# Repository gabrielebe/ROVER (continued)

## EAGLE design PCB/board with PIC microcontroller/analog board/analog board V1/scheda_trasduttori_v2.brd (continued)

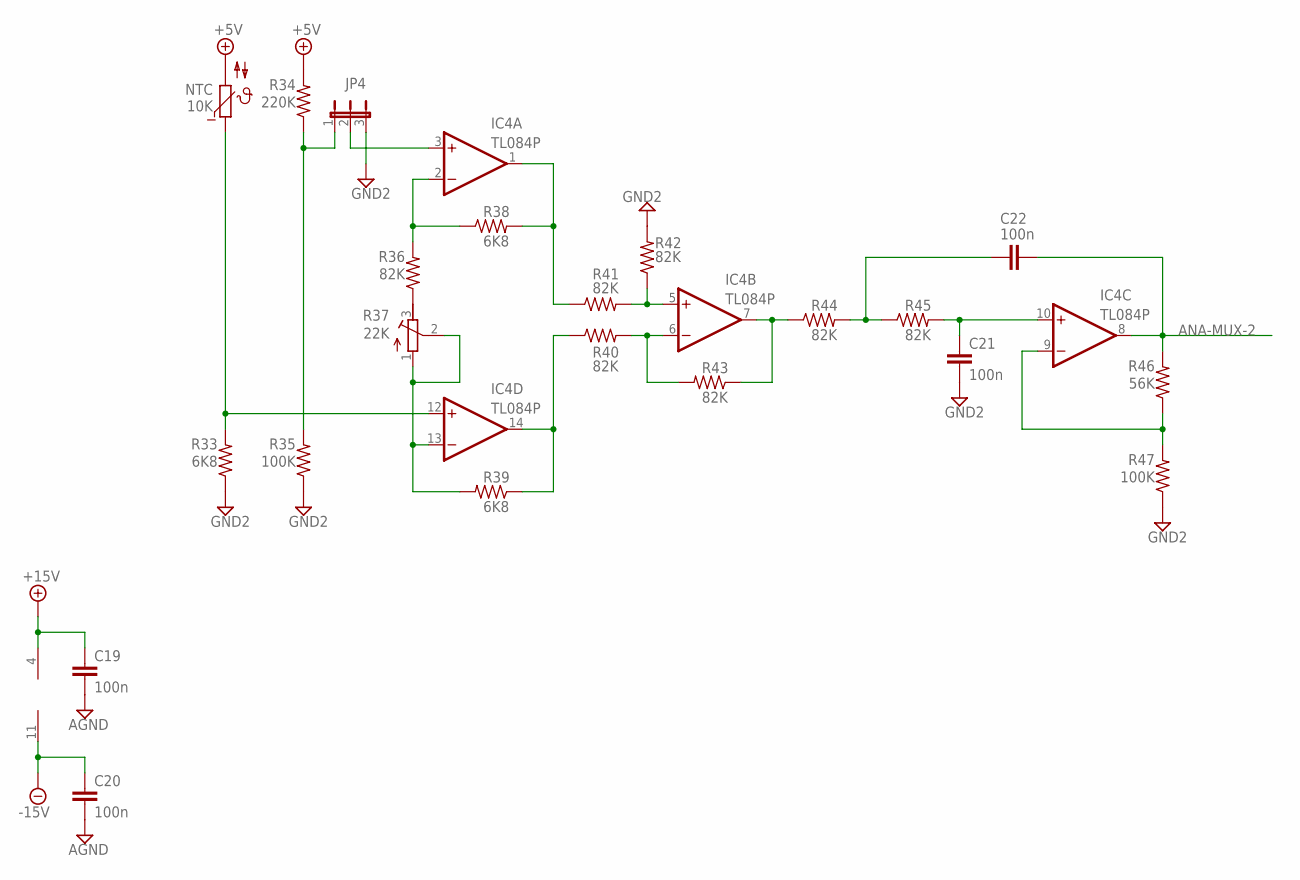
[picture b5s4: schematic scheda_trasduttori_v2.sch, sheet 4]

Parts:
C19, C20, C21, C22: 100n; C025-025X050
IC4: TL084P; DIL14
JP4: JP2E; JP2
NTC: 10K; P640
R33, R38, R39: 6K8; 0204/7
R34: 220K; 0204/7
R35, R47: 100K; 0204/7
R36, R40, R41, R42, R43, R44, R45: 82K; 0204/7
R37: 22K; RTRIM64W
R46: 56K; 0204/7

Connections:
+5V: NTC.2, R34.2; also elsewhere on the board
+15V: C19.1, IC4.4 (V+); also elsewhere on the board
-15V: C20.1, IC4.11 (V-); also elsewhere on the board
AGND: C19.2, C20.2; also elsewhere on the board
ANA-MUX-2: C22.2, IC4.8 (OUT), R46.2; also elsewhere on the board
GND2: C21.2, JP4.3, R33.1, R35.1, R42.2, R47.1; also elsewhere on the board
unnamed: C21.1, IC4.10 (+IN), R45.2
unnamed: IC4.9 (-IN), R46.1, R47.2
unnamed: C22.1, R44.2, R45.1
unnamed: IC4.12 (+IN), NTC.1, R33.2
unnamed: R36.1, R37.3 (A)
unnamed: IC4.2 (-IN), R36.2, R38.1
unnamed: IC4.1 (OUT), R38.2, R40.1
unnamed: IC4.13 (-IN), R37.1 (E), R37.2 (S), R39.2
unnamed: IC4.14 (OUT), R39.1, R41.1
unnamed: IC4.6 (-IN), R41.2, R43.2
unnamed: IC4.5 (+IN), R40.2, R42.1
unnamed: IC4.7 (OUT), R43.1, R44.1
unnamed: JP4.1, R34.1, R35.2
unnamed: IC4.3 (+IN), JP4.2

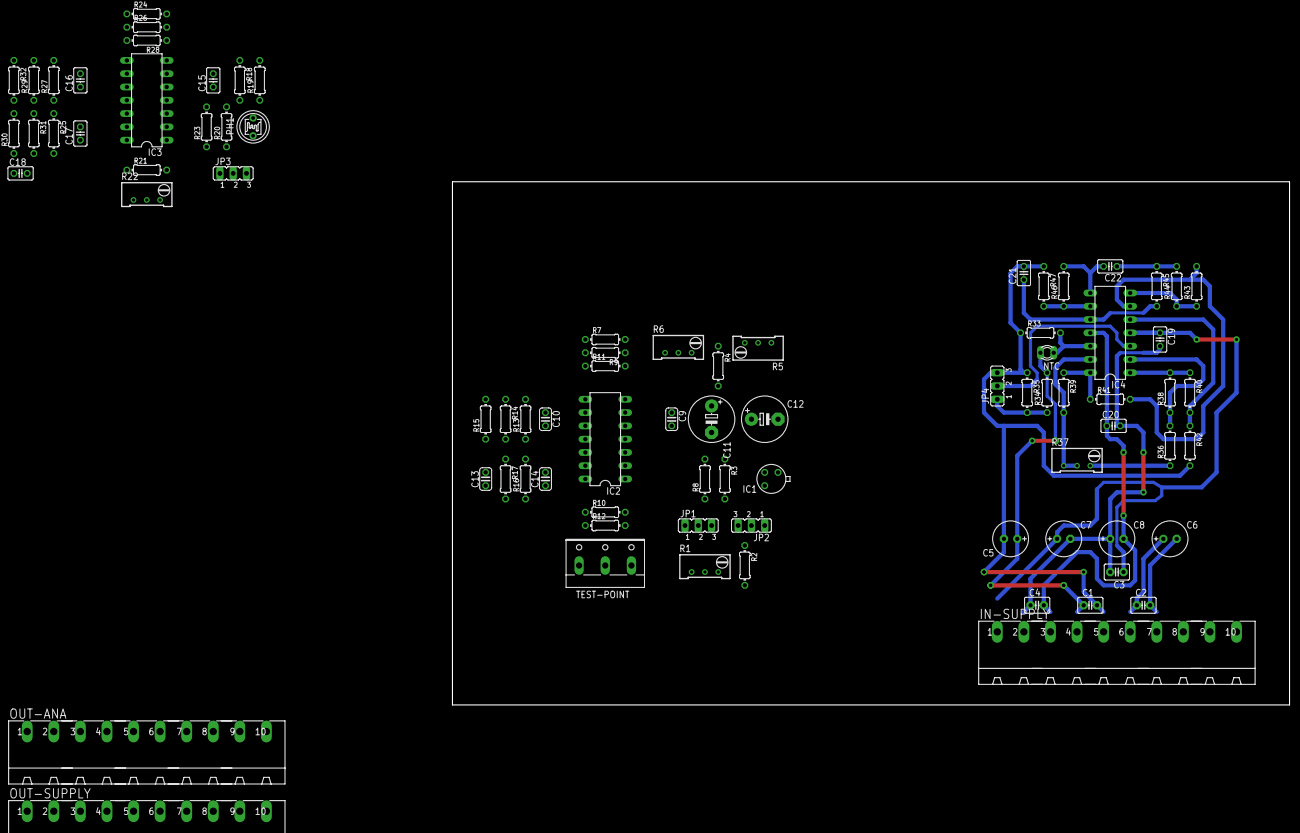
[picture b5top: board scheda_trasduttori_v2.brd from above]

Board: 2 copper layers, 160.0 x 100.0 mm, 83 parts (0 on the bottom side), 56 nets.

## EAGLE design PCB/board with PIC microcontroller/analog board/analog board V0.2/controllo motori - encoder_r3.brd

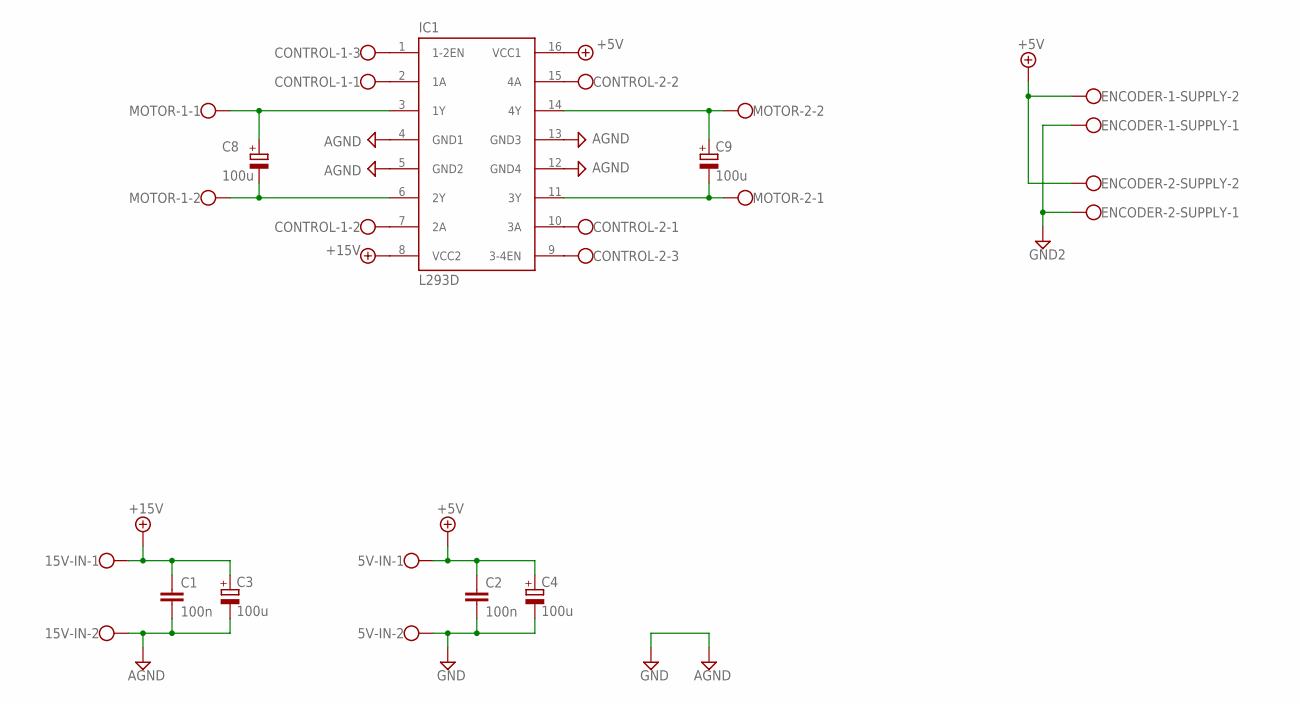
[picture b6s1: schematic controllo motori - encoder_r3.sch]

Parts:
5V-IN, 15V-IN: W237-102
C1, C2: 100n; C025-025X050
C3, C4, C8, C9: 100u; B45181B
CONTROL-1, CONTROL-2: W237-103
ENCODER-1-SUPPLY, ENCODER-2-SUPPLY: W237-102
IC1: L293D; DIL16
MOTOR-1, MOTOR-2: W237-102

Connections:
+5V: 5V-IN.1, C2.1, C4.+, ENCODER-1-SUPPLY.2, ENCODER-2-SUPPLY.2, IC1.16 (VCC1)
+15V: 15V-IN.1, C1.1, C3.+, IC1.8 (VCC2)
AGND: 15V-IN.2, C1.2, C3.-, IC1.4 (GND1), IC1.5 (GND2), IC1.12 (GND4), IC1.13 (GND3)
GND: 5V-IN.2, C2.2, C4.-
GND2: ENCODER-1-SUPPLY.1, ENCODER-2-SUPPLY.1
unnamed: C8.+, IC1.3 (1Y), MOTOR-1.1
unnamed: C8.-, IC1.6 (2Y), MOTOR-1.2
unnamed: C9.-, IC1.11 (3Y), MOTOR-2.1
unnamed: C9.+, IC1.14 (4Y), MOTOR-2.2
unnamed: CONTROL-1.1, IC1.2 (1A)
unnamed: CONTROL-1.2, IC1.7 (2A)
unnamed: CONTROL-1.3, IC1.1 (1-2EN)
unnamed: CONTROL-2.3, IC1.9 (3-4EN)
unnamed: CONTROL-2.1, IC1.10 (3A)
unnamed: CONTROL-2.2, IC1.15 (4A)

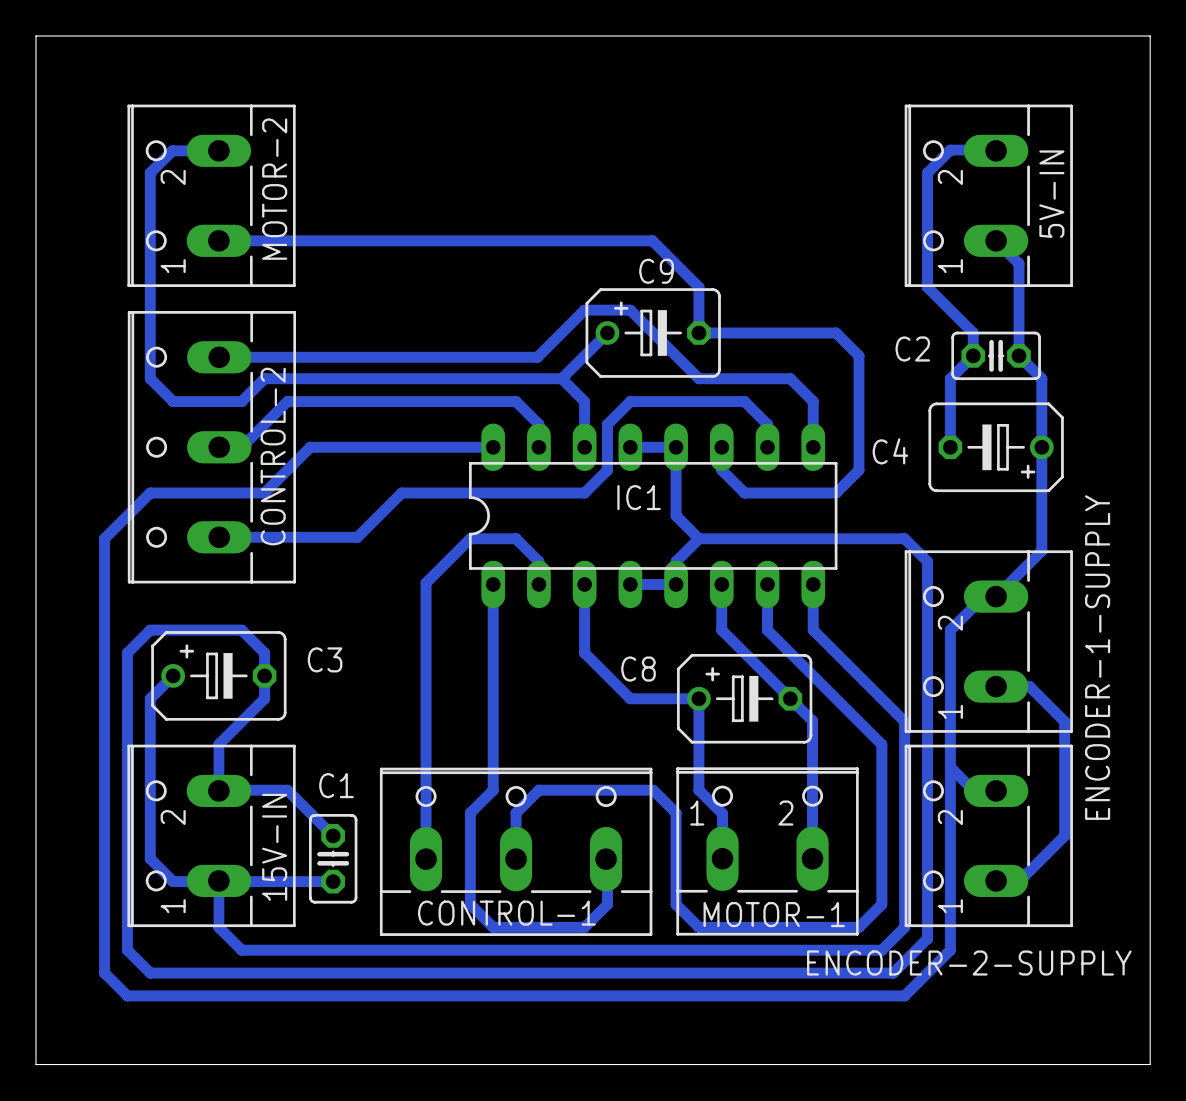
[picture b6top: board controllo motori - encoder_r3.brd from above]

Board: 2 copper layers, 61.9 x 57.1 mm, 15 parts (0 on the bottom side), 15 nets.

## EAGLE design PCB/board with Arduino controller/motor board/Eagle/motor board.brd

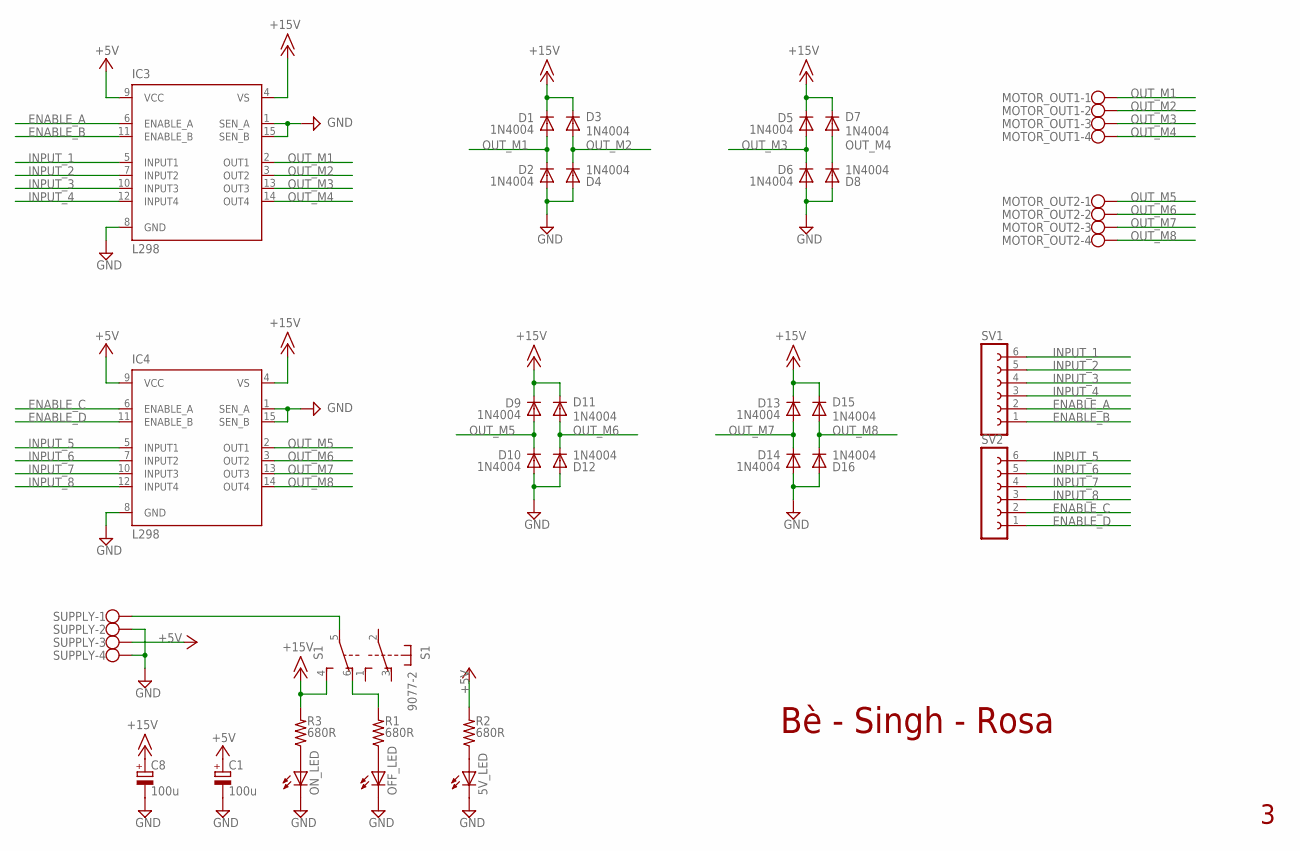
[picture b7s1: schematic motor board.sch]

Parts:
5V_LED: LED5MM
C1: 100u; E2,5-7
C8: 100u; E3,5-8
D1, D2, D3, D4, D5, D6, D7, D8, D9, D10, D11, D12, D13, D14, D15, D16: 1N4004; DO41-10
IC3, IC4: L298; MULTIWATT-15
MOTOR_OUT1, MOTOR_OUT2: W237-4
OFF_LED: LED5MM
ON_LED: LED5MM
R1, R2, R3: 680R; 0207/10
S1: 9077-2
SUPPLY: W237-4
SV1, SV2: FE06-1; FE06

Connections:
+5V: C1.+, IC3.9 (VCC), IC4.9 (VCC), R2.2, SUPPLY.3
+15V: C8.+, D1.C, D3.C, D5.C, D7.C, D9.C, D11.C, D13.C, D15.C, IC3.4 (VS), IC4.4 (VS), R3.2, S1.4 (S)
ENABLE_A: IC3.6 (ENABLE_A), SV1.2
ENABLE_B: IC3.11 (ENABLE_B), SV1.1
ENABLE_C: IC4.6 (ENABLE_A), SV2.2
ENABLE_D: IC4.11 (ENABLE_B), SV2.1
GND: 5V_LED.K (C), C1.-, C8.-, D2.A, D4.A, D6.A, D8.A, D10.A, D12.A, D14.A, D16.A, IC3.1 (SEN_A), IC3.8 (GND), IC3.15 (SEN_B), IC4.1 (SEN_A), IC4.8 (GND), IC4.15 (SEN_B), OFF_LED.K (C), ON_LED.K (C), SUPPLY.2, SUPPLY.4
INPUT_1: IC3.5 (INPUT1), SV1.6
INPUT_2: IC3.7 (INPUT2), SV1.5
INPUT_3: IC3.10 (INPUT3), SV1.4
INPUT_4: IC3.12 (INPUT4), SV1.3
INPUT_5: IC4.5 (INPUT1), SV2.6
INPUT_6: IC4.7 (INPUT2), SV2.5
INPUT_7: IC4.10 (INPUT3), SV2.4
INPUT_8: IC4.12 (INPUT4), SV2.3
unnamed: ON_LED.A, R3.1
unnamed: OFF_LED.A, R1.1
unnamed: 5V_LED.A, R2.1
unnamed: S1.5, SUPPLY.1
unnamed: R1.2, S1.6 (O)
OUT_M1: D1.A, D2.C, IC3.2 (OUT1), MOTOR_OUT1.1
OUT_M2: D3.A, D4.C, IC3.3 (OUT2), MOTOR_OUT1.2
OUT_M3: D5.A, D6.C, IC3.13 (OUT3), MOTOR_OUT1.3
OUT_M4: D7.A, D8.C, IC3.14 (OUT4), MOTOR_OUT1.4
OUT_M5: D9.A, D10.C, IC4.2 (OUT1), MOTOR_OUT2.1
OUT_M6: D11.A, D12.C, IC4.3 (OUT2), MOTOR_OUT2.2
OUT_M7: D13.A, D14.C, IC4.13 (OUT3), MOTOR_OUT2.3
OUT_M8: D15.A, D16.C, IC4.14 (OUT4), MOTOR_OUT2.4

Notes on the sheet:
Bè - Singh - Rosa

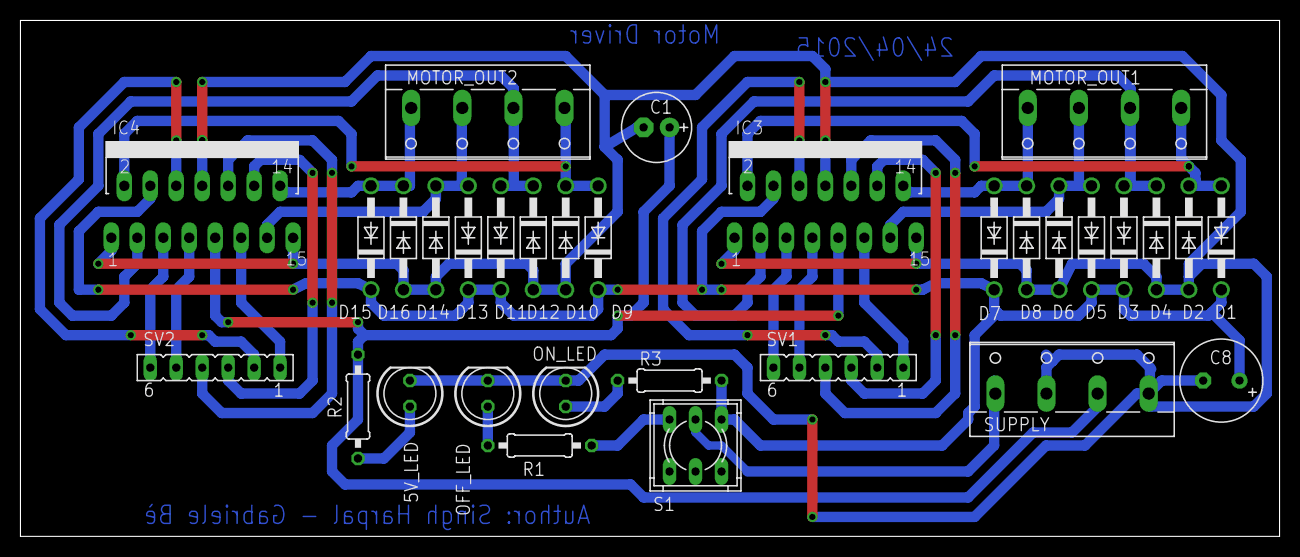
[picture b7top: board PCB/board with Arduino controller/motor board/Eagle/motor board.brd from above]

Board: 2 copper layers, 123.2 x 50.5 mm, 32 parts (0 on the bottom side), 28 nets.

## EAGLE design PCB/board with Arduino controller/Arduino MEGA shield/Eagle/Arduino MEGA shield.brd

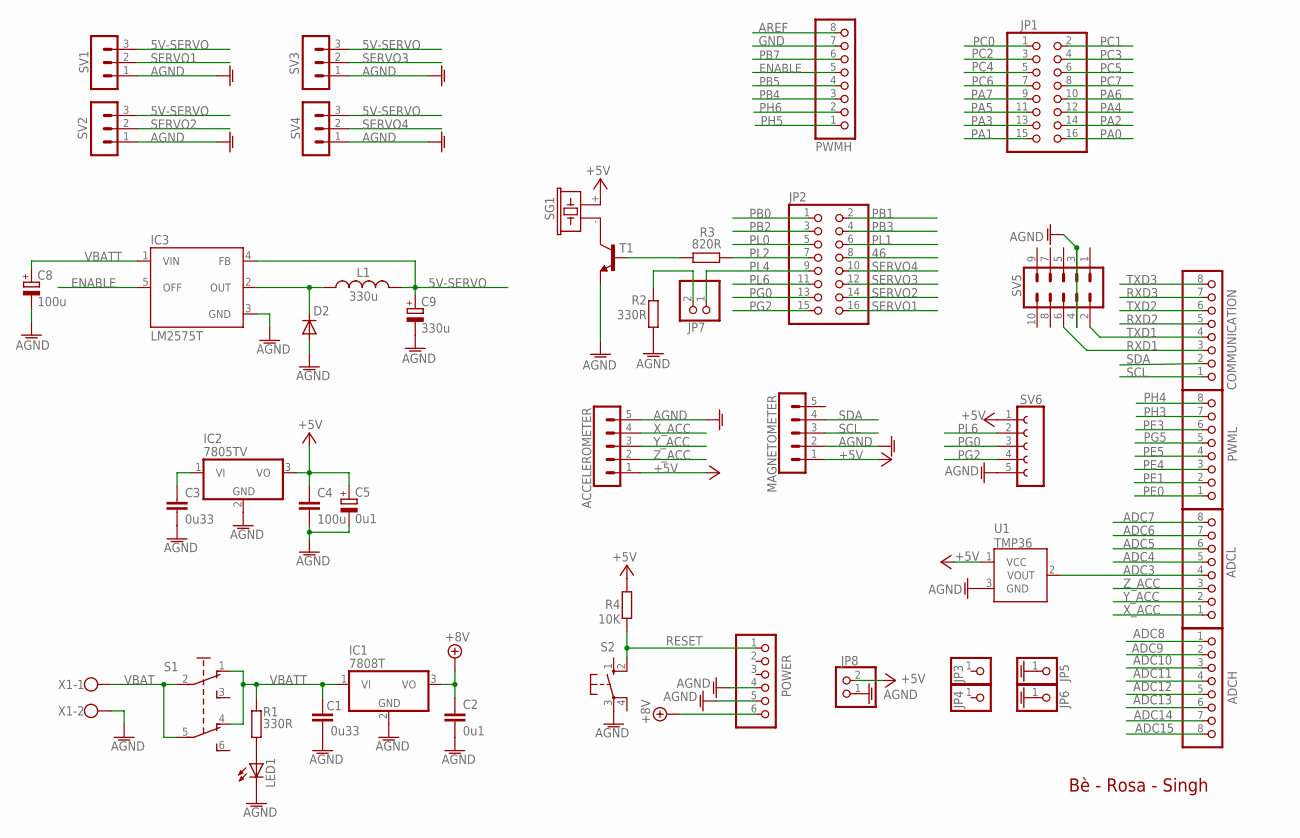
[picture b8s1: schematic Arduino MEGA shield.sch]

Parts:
ACCELEROMETER: MA05-1
ADCH: PINHD-1X8; 1X08
ADCL: PINHD-1X8; 1X08
C1, C3: 0u33; C050-035X075
C2: 0u1; C050-035X075
C4: 100u; C050-035X075
C5: 0u1; E2,5-7
C8: 100u; E3,5-8
C9: 330u; E3,5-8
COMMUNICATION: PINHD-1X8; 1X08
D2: 1N5819; DO35-10
IC1: 7808T; TO220H
IC2: 7805TV; TO220V
IC3: LM2575T; TO220-5
JP1, JP2: PINHD-2X8; 2X08
JP3, JP4, JP5, JP6: PINHD-1X1; 1X01
JP7, JP8: PINHD-1X2; 1X02
L1: 330u; AXIAL-0.6
LED1: LED5MM
MAGNETOMETER: MA05-1
POWER: PINHD-1X6; 1X06
PWMH: PINHD-1X8; 1X08
PWML: PINHD-1X8; 1X08
R1, R2: 330R; 0207/10
R3: 820R; 0207/10
R4: 10K; 0207/10
S1: TL46PO; TL4XPO
S2: 10-XX; B3F-10XX
SG1: F/CM12P
SV1, SV2, SV3, SV4: MA03-1
SV5: MA05-2
SV6: FE05-1
T1: BC547A-NPN-TO92-CBE; TO92-CBE
U1: TMP36; TO-92
X1: W237-102

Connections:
5V-SERVO: C9.+, IC3.4 (FB), L1.P$2 (2), SV1.3, SV2.3, SV3.3, SV4.3
46: JP2.8
+5V: ACCELEROMETER.1, C4.1, C5.+, IC2.3 (VO), JP8.2, MAGNETOMETER.1, R4.2, SG1.+ (1), SV6.1, U1.1 (VCC)
+8V: C2.1, IC1.3 (VO), POWER.6
ADC3: ADCL.4, U1.2 (VOUT)
ADC4: ADCL.5
ADC5: ADCL.6
ADC6: ADCL.7
ADC7: ADCL.8
ADC8: ADCH.1
ADC9: ADCH.2
ADC10: ADCH.3
ADC11: ADCH.4
ADC12: ADCH.5
ADC13: ADCH.6
ADC14: ADCH.7
ADC15: ADCH.8
AGND: ACCELEROMETER.5, C1.2, C2.2, C3.2, C4.2, C5.-, C8.-, C9.-, D2.A, IC1.2 (GND), IC2.2 (GND), IC3.3 (GND), JP5.1, JP6.1, JP8.1, LED1.K (C), MAGNETOMETER.2, POWER.4, POWER.5, R2.2, S2.3, SV1.1, SV2.1, SV3.1, SV4.1, SV5.3, SV5.4, SV6.5, T1.E, U1.3 (GND), X1.2
AREF: PWMH.8
ENABLE: IC3.5 (OFF), PWMH.5
GND: PWMH.7
unnamed: JP7.2, R2.1
unnamed: LED1.A, R1.1
unnamed: C3.1, IC2.1 (VI)
unnamed: R3.1, T1.B
unnamed: D2.C, IC3.2 (OUT), L1.P$1 (1)
unnamed: SG1.- (2), T1.C
PA0: JP1.16
PA1: JP1.15
PA2: JP1.14
PA3: JP1.13
PA4: JP1.12
PA5: JP1.11
PA6: JP1.10
PA7: JP1.9
PB0: JP2.1
PB1: JP2.2
PB2: JP2.3
PB3: JP2.4
PB4: PWMH.3
PB5: PWMH.4
PB7: PWMH.6
PC0: JP1.1
PC1: JP1.2
PC2: JP1.3
PC3: JP1.4
PC4: JP1.5
PC5: JP1.6
PC6: JP1.7
PC7: JP1.8
PE0: PWML.1
PE1: PWML.2
PE3: PWML.6
PE4: PWML.3
PE5: PWML.4
PG0: JP2.13, SV6.3
PG2: JP2.15, SV6.4
PG5: PWML.5
PH3: PWML.7
PH4: PWML.8
PH5: PWMH.1
PH6: PWMH.2
PL0: JP2.5
PL1: JP2.6
PL2: JP2.7, R3.2
PL4: JP2.9, JP7.1
PL6: JP2.11, SV6.2
RESET: POWER.1, R4.1, S2.2 (S1)
RXD1: COMMUNICATION.3, SV5.6
RXD2: COMMUNICATION.5
RXD3: COMMUNICATION.7
SCL: COMMUNICATION.1, MAGNETOMETER.3
SDA: COMMUNICATION.2, MAGNETOMETER.4
SERVO1: JP2.16, SV1.2
SERVO2: JP2.14, SV2.2
SERVO3: JP2.12, SV3.2
SERVO4: JP2.10, SV4.2
TXD1: COMMUNICATION.4, SV5.2
TXD2: COMMUNICATION.6
TXD3: COMMUNICATION.8
VBAT: S1.2, S1.5 (P1), X1.1
VBATT: C1.1, C8.+, IC1.1 (VI), IC3.1 (VIN), R1.2, S1.1 (O), S1.4 (O1)
X_ACC: ACCELEROMETER.4, ADCL.1
Y_ACC: ACCELEROMETER.3, ADCL.2
Z_ACC: ACCELEROMETER.2, ADCL.3

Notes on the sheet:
Bè - Rosa - Singh

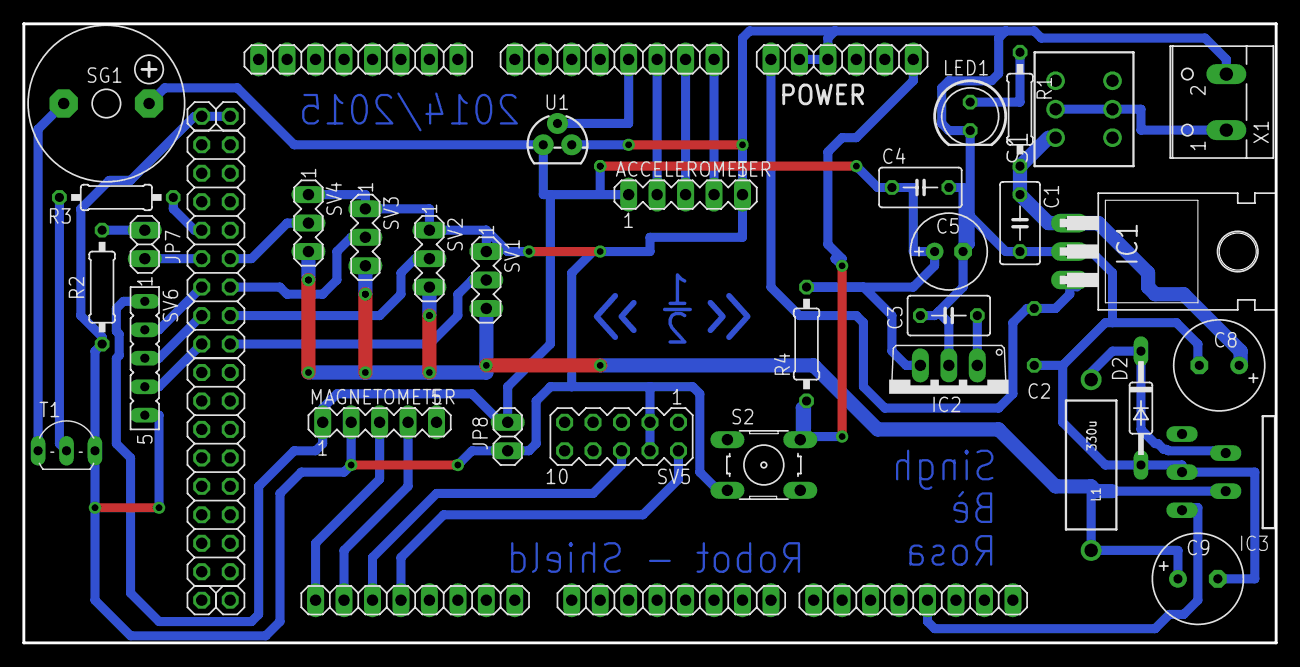
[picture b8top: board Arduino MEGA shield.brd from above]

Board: 2 copper layers, 111.8 x 55.2 mm, 45 parts (1 on the bottom side), 31 nets.

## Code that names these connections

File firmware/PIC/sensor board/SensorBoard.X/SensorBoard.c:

/* 
 * File:   SensorBoard.c
 * Author: Harpal
 *
 * Created on 23 gennaio 2015, 12.10
 */

#include <stdio.h>
#include <stdlib.h>
#include "Analog.h"

// PIC16F886 Configuration Bit Settings

// 'C' source line config statements

#include <xc.h>

// #pragma config statements should precede project file includes.
// Use project enums instead of #define for ON and OFF.

// CONFIG1
#pragma config FOSC = EXTRC_NOCLKOUT// Oscillator Selection bits (RCIO oscillator: I/O function on RA6/OSC2/CLKOUT pin, RC on RA7/OSC1/CLKIN)
#pragma config WDTE = OFF       // Watchdog Timer Enable bit (WDT disabled and can be enabled by SWDTEN bit of the WDTCON register)
#pragma config PWRTE = ON       // Power-up Timer Enable bit (PWRT enabled)
#pragma config MCLRE = ON       // RE3/MCLR pin function select bit (RE3/MCLR pin function is MCLR)
#pragma config CP = OFF         // Code Protection bit (Program memory code protection is disabled)
#pragma config CPD = OFF        // Register Code Protection bit (Register memory code protection is disabled)
#pragma config BOREN = ON       // Brown Out Reset Selection bits (BOR enabled)
#pragma config IESO = ON        // Internal External Switchover bit (Internal/External Switchover mode is enabled)
#pragma config FCMEN = ON       // Fail-Safe Clock Monitor Enabled bit (Fail-Safe Clock Monitor is enabled)
#pragma config LVP = OFF        // Low Voltage Programming Enable bit (RB3 pin has digital I/O, HV on MCLR must be used for programming)

// CONFIG2
#pragma config BOR4V = BOR40V   // Brown-out Reset Selection bit (Brown-out Reset set to 4.0V)
#pragma config WRT = OFF        // Flash Program Memory Self Write Enable bits (Write protection off)

#define _XTAL_FREQ  8000000
#define ADDR_BASE   0b01110000

#ifndef ADDR_PIN1
#define ADDR_PIN1           (PORTCbits.RC0)
#define ADDR_PIN1_DIR       (TRISCbits.TRISC0)
#endif

#ifndef ADDR_PIN2
#define ADDR_PIN2           (PORTCbits.RC1)
#define ADDR_PIN2_DIR       (TRISCbits.TRISC1)
#endif

#ifndef STATUS_LED
#define STATUS_LED          (PORTCbits.RC5)
#define STATUS_LED_DIR      (TRISCbits.TRISC5)
#endif



/* Function prototypes are declared here */
void config(void);
void initialize_i2c(void);
void interrupt ISR(void);
unsigned char sendMaster(void);
void receiveData(void);
void fillRegister(char);

/* Global variables are declared here */
volatile unsigned char junk, I2C_receivedByte, I2C_sendByte;
int counter = 1;
/* Communication variables */
enum {
    index,
    tempL,
    tempH,
    accXL,
    accXH,
    accYL,
    accYH,
    accZL,
    accZH,
    lightL,
    lightH,
    configuration,
    status,
    last
};

enum {
    Temprature,
    Light,
    Accelerometer
};

char Register[last] = {0};

int main(int argc, char** argv) {
    config();
    initialize_i2c();
    tempCalibration();
    STATUS_LED_DIR = 0;
    while (1) {
        STATUS_LED = 1;
        fillRegister(Temprature);
        fillRegister(Light);
        fillRegister(Accelerometer);
    }

    return (EXIT_SUCCESS);
}

void config(void) {
    //setting the oscillator to 8 MHz
    OSCCONbits.IRCF0 = 1;
    OSCCONbits.IRCF1 = 1;
    OSCCONbits.IRCF2 = 1;

    //setting by default the internal clock source for the system
    OSCCONbits.SCS = 1;

    //Setting the port b as digital
    ANSELH = 0x00;

    STATUS_LED_DIR = 0;
}

void interrupt ISR(void) // Interrupt Service Routine
{
    if (SSPIF) // I2C interrupt
    {
        STATUS_LED = 0;
        if (!D_A && !R_W && BF) // An address from master: write to slave
        {
            junk = SSPBUF; // Empty buffer and clear BF bit

        } else if (D_A && !R_W && BF) // Register from master to slave
        {
            receiveData();   //Go to the function that handles the reception from master

        } else if (!D_A && R_W && !BF) // An address from master: read from slave
        {
            SSPBUF = Register[tempL]; // Register will be write to master
            CKP = 1; // Release clock (Register ready to be send to master)
        } else if (D_A && R_W && !BF) // Read a byte from slave (next byte)
        {
            SSPBUF = Register[tempL]; // Register will be write to master
            CKP = 1; // Release clock (Register ready to be send to master)
        } else if (D_A && !R_W && !BF) // NAK from master (complete transmission has occurred)
        {
            counter = 1;    //clear the counter
        }
    }
    SSPIF = 0; // Re-enable interrupt
}
void fillRegister(char array) {

    switch (array) {
        case Temprature:
            Register[tempL] = (0x00ff & (int)readTemp());
            Register[tempH] = ((int)readTemp() >> 8)&0x00ff;
            break;

        case Light:
            Register[lightL] = 0x00ff & (int)readLight();
            Register[lightH] = ((int)readLight() >> 8)&0x00ff;
            break;

        case Accelerometer:
            Register[accXL] = 0x00ff & (int)readAccelerometer(CHANNEL_X_AXIS);
            Register[accXH] = ((int)readAccelerometer(CHANNEL_X_AXIS) >> 8)&0x00ff;
            Register[accYL] = 0x00ff & (int)readAccelerometer(CHANNEL_Y_AXIS);
            Register[accYH] = ((int)readAccelerometer(CHANNEL_Y_AXIS) >> 8)&0x00ff;
            Register[accZL] = 0x00ff & (int)readAccelerometer(CHANNEL_Z_AXIS);
            Register[accZH] = ((int)readAccelerometer(CHANNEL_Z_AXIS) >> 8)&0x00ff;
    }
}

void receiveData(void)
{
    if(counter == 1)
    {
        Register[index] = SSPBUF;
        counter++;
    }
    else
    {
        Register[Register[index]] = SSPBUF;
        counter++;
    }
}

unsigned char sendMaster(void)
{
    static char indexCounter = 0;
    if(!(Register[index] < last && Register[index] > index))
    {
        Register[index] = 1;
        indexCounter = 0;
    }
    switch(indexCounter)
    {
        case 0:
            indexCounter++;
            return Register[tempL];
            
        case 1:
            indexCounter++;
            return Register[tempH];
            
        case 2:
            indexCounter++;
            return Register[lightL];
            
        case 3:
            indexCounter++;
            return Register[lightH];
            
        case 4:
            indexCounter++;
            return Register[accXL];
            
        case 5:
            indexCounter++;
            return Register[accXH];
            
        case 6:
            indexCounter++;
            return Register[accYL];
            
        case 7:
            indexCounter++;
            return Register[accYH];
            
        case 8:
            indexCounter++;
            return Register[accZL];
            
        case 9:
            indexCounter++;
            return Register[accZH];
            
        case 10:
            indexCounter = 0;
            return Register[status];
        default:
            return -10;
    }
}

void initialize_i2c(void) {
    //setting the SDA and SCL pin as input
    TRISCbits.TRISC3 = 1; //SCL pin
    TRISCbits.TRISC4 = 1; //SDA pin

    //enabling the slew rate mode to work at 400KHz
    SSPSTATbits.SMP = 0;

    //don't care about the write collision
    SSPCONbits.WCOL = 0;

    //dont' care about the oveerflow condition
    SSPCONbits.SSPOV = 0;


    //selecting the funztion mode as I2C slave with 7 bit address
    //without any interrupt on start and stop
    SSPCONbits.SSPM0 = 0;
    SSPCONbits.SSPM1 = 1;
    SSPCONbits.SSPM2 = 1;
    SSPCONbits.SSPM3 = 0;
    SSPCONbits.CKP = 1; //release the clock
    SSPCONbits.SSPEN = 1; //enable the module

    ADDR_PIN1_DIR = 1;
    ADDR_PIN2_DIR = 1;

    // Setting the adress of the devices
    SSPADD = ((ADDR_PIN1) | (ADDR_PIN2 << 1) | ADDR_BASE) << 1;

    //disable  the general call (?)
    SSPCON2bits.GCEN = 0;

    //enabling the intterrupt
    PIE1bits.SSPIE = 1;

    //clearing the intterrupt flag
    PIR1bits.SSPIF = 0;
}

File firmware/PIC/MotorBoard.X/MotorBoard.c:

/* 
 * File:   SensorBoard.c
 * Author: Harpal
 *
 * Created on 23 gennaio 2015, 12.10
 */

#include <stdio.h>
#include <stdlib.h>
#include <xc.h>
#include "Motor.h"

// #pragma config statements should precede project file includes.
// Use project enums instead of #define for ON and OFF.

// CONFIG1
#pragma config FOSC = EXTRC_NOCLKOUT// Oscillator Selection bits (RCIO oscillator: I/O function on RA6/OSC2/CLKOUT pin, RC on RA7/OSC1/CLKIN)
#pragma config WDTE = OFF       // Watchdog Timer Enable bit (WDT disabled and can be enabled by SWDTEN bit of the WDTCON register)
#pragma config PWRTE = ON       // Power-up Timer Enable bit (PWRT enabled)
#pragma config MCLRE = ON       // RE3/MCLR pin function select bit (RE3/MCLR pin function is MCLR)
#pragma config CP = OFF         // Code Protection bit (Program memory code protection is disabled)
#pragma config CPD = OFF        // Data Code Protection bit (Data memory code protection is disabled)
#pragma config BOREN = ON       // Brown Out Reset Selection bits (BOR enabled)
#pragma config IESO = ON        // Internal External Switchover bit (Internal/External Switchover mode is enabled)
#pragma config FCMEN = ON       // Fail-Safe Clock Monitor Enabled bit (Fail-Safe Clock Monitor is enabled)
#pragma config LVP = OFF        // Low Voltage Programming Enable bit (RB3 pin has digital I/O, HV on MCLR must be used for programming)

// CONFIG2
#pragma config BOR4V = BOR40V   // Brown-out Reset Selection bit (Brown-out Reset set to 4.0V)
#pragma config WRT = OFF        // Flash Program Memory Self Write Enable bits (Write protection off)

#define _XTAL_FREQ  8000000
#define ADDR_BASE   0b01010000

#ifndef ADDR_PIN1
#define ADDR_PIN1           (PORTBbits.RB0)
#define ADDR_PIN1_DIR       (TRISBbits.TRISB0)
#endif

#ifndef ADDR_PIN2
#define ADDR_PIN2           (PORTBbits.RB1)
#define ADDR_PIN2_DIR       (TRISBbits.TRISB1)
#endif


/* Function prototypes are declared here */

void config(void);
void initialize_i2c(void);
void interrupt ISR(void);


/* Global variables are declared here */

volatile unsigned char junk, I2C_receivedByte, I2C_sendByte;



int main(int argc, char** argv) {
    config();
    initialize_i2c();

    while (1)
    {

    }

    return (EXIT_SUCCESS);
}


void config(void) {
    //setting the oscillator to 8 MHz
    OSCCONbits.IRCF0 = 1;
    OSCCONbits.IRCF1 = 1;
    OSCCONbits.IRCF2 = 1;
    
    //setting by default the internal clock source for the system
    OSCCONbits.SCS = 1;

    //setting the port b as digital
    ANSELH = 0x00;
}


void initialize_i2c(void) {
    //setting the SDA and SCL pin as input
    TRISCbits.TRISC3 = 1; //SCL pin
    TRISCbits.TRISC4 = 1; //SDA pin

    //enabling the slew rate mode to work at 400KHz
    SSPSTATbits.SMP = 0;

    //don't care about the write collision
    SSPCONbits.WCOL = 0;

    //dont' care about the oveerflow condition
    SSPCONbits.SSPOV = 0;

    //selecting the funztion mode as I2C slave with 7 bit address
    //without any interrupt on start and stop
    SSPCONbits.SSPM0 = 0;
    SSPCONbits.SSPM1 = 1;
    SSPCONbits.SSPM2 = 1;
    SSPCONbits.SSPM3 = 0;
    SSPCONbits.CKP = 1; //release the clock
    SSPCONbits.SSPEN = 1; //enable the module

    ADDR_PIN1_DIR = 1;
    ADDR_PIN2_DIR = 1;

    //setting the adress of the devices
    SSPADD = ((ADDR_PIN1)|(ADDR_PIN2<<1)|ADDR_BASE) << 1;

    //disable  the general call (?)
    SSPCON2bits.GCEN = 0;

    //enabling the intterrupt
    PIE1bits.SSPIE = 1;

    //clearing the intterrupt flag
    PIR1bits.SSPIF = 0;
}


// Interrupt Service Routine
void interrupt ISR(void)
{
    if (SSPIF) // I2C interrupt
    {
        if (!D_A && !R_W && BF) // An address from master: write to slave
        {
            junk = SSPBUF; // Empty buffer and clear BF bit

        } else if (D_A && !R_W && BF) // Data from master to slave
        {
            I2C_receivedByte = SSPBUF; // Output data to PORTC LEDs and clear BF bit

        } else if (!D_A && R_W && !BF) // An address from master: read from slave
        {
            SSPBUF = I2C_sendByte; // Data will be write to master
            CKP = 1; // Release clock (data ready to be send to master)
        } else if (D_A && R_W && !BF) // Read a byte from slave (next byte)
        {
            SSPBUF = I2C_sendByte; // Data will be write to master
            CKP = 1; // Release clock (data ready to be send to master)
        } else if (D_A && !R_W && !BF) // NAK from master (complete transmission has occurred)
        {
        }
    }
    SSPIF = 0; // Re-enable interrupt
}

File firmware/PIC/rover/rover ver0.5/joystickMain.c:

/* 
 * File:   joystickMain.c
 * Author: Harpal
 *
 * Created on 28 novembre 2014, 11.53
 */

#include <stdio.h>
#include <stdlib.h>
#include<pic16f628a.h>

// PIC16F628A Configuration Bit Settings

// 'C' source line config statements

#include <xc.h>
#define _XTAL_FREQ 16000000
// #pragma config statements should precede project file includes.
// Use project enums instead of #define for ON and OFF.

// CONFIG
#pragma config FOSC = EXTRCCLK  // Oscillator Selection bits (RC oscillator: CLKOUT function on RA6/OSC2/CLKOUT pin, Resistor and Capacitor on RA7/OSC1/CLKIN)
#pragma config WDTE = OFF       // Watchdog Timer Enable bit (WDT disabled)
#pragma config PWRTE = ON       // Power-up Timer Enable bit (PWRT enabled)
#pragma config MCLRE = OFF      // RA5/MCLR/VPP Pin Function Select bit (RA5/MCLR/VPP pin function is digital input, MCLR internally tied to VDD)
#pragma config BOREN = ON       // Brown-out Detect Enable bit (BOD enabled)
#pragma config LVP = OFF        // Low-Voltage Programming Enable bit (RB4/PGM pin has digital I/O function, HV on MCLR must be used for programming)
#pragma config CPD = OFF        // Data EE Memory Code Protection bit (Data memory code protection off)
#pragma config CP = OFF         // Flash Program Memory Code Protection bit (Code protection off)


/*
 * 
 */
#define STRLEN 20
void USART_init();
void sendByte(char Byte);
void sendString(char *s);

volatile unsigned char t = 0;
volatile unsigned char rcindex = 0;
volatile unsigned char rcbuf[STRLEN];

int main(int argc, char** argv) {
    USART_init();
    __delay_ms(50);
    sendString("Comunication is ok\n");
    INTCONbits.PEIE = 1;    // enable peripheral interrupts
    INTCONbits.GIE = 1;     // enable interrupts

    while(1)
    {

    }
    return (EXIT_SUCCESS);
}

void USART_init() {
    TRISBbits.TRISB1 = 1;
    TRISBbits.TRISB2 = 1;
    TXSTAbits.TXEN = 1;
    TXSTAbits.BRGH = 1;
    SPBRG = 104;
    TXSTAbits.SYNC = 0;
    RCSTAbits.SPEN = 1;
    RCSTAbits.CREN = 1;

    PIE1bits.RCIE = 1;

}
void sendByte(unsigned char Byte) {
    while (TXSTAbits.TRMT == 0);
    TXREG = Byte;
}

void sendString(unsigned char *s) {
    while (*s) {
        sendByte(*s);
        __delay_us(10);
        s++;
    }
}

void interrupt ISR(void) {
    if (PIR1bits.RCIF) // check if receive interrupt has fired
    {
        t = RCREG; // read received character to buffer

        // check if received character is not new line character
        // and that maximum string length has not been reached
        if ((t != '\n') && (rcindex < STRLEN)) {
            rcbuf[rcindex] = t; // append received character to string
            rcindex++; // increment string index
        }
        else {
            rcindex = 0; // reset string index
            sendString(rcbuf); // echo received string
            sendByte('\n');
            for(int i = 0; i < STRLEN; i++)
                rcbuf[i] = 0;
        }


        PIR1bits.RCIF = 0; // reset receive interrupt flag
    }
}

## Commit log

2015-06-15 relase 1.0
